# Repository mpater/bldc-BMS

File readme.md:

# VESC BMS
## Overview
Battery Managment System (BMS) for (but not limited to) an Electronic Speed Controller, specifically for a longboard controller (VESC). 

Current battery pack specifications are LiFePO4 (3.2V nominal, ~2.6Ah) in a 6s2p, giving 19.2V with 5Ah (96Wh). Continuous discharge is about 20A (384W) with 30 second pulse discharge of 52A (1kW) and charge current of 5.2A (21.9V), for a 2p configuration.

Scope of the project is to design a BMS to meet the above specifications using off-the-shelf ICs for the battery managment section. A microcontroller circuit would also be incorperated to allow communication between the BMS and controller (SMBus/I2C), contrller and PC (USB-serial) and contrller and VESC (CAN bus).

Texis Instruments (TI) appears to have the most comprehensive set of battery managment systems offerings. These appear to be split up into two main sections: cell monitors and gas gauges. 
The bq769x0 seires will be used for the cell monitoring, offering bq76920, bq76930 and bq76940 based on the pack size. 
Currently the top candidats for the gas gauge are bq78350-R1 and bq34z100-R1 but more research is needed to determine which one is better suited. 

## BMS
- **Cell Monitor**
  - Measure cell voltages and pack current (Coulomb Counter)
  - Cell and temperature measurment
  - Charge Limit (over-voltage and over-amperage)
  - Discharge Limit (under-Voltage and over-amperage)
  - Balancing circuitry and autobalancing mode
  - 
- **'Gas Gauge' and Battery Managment Controller**
  - Estimate pack State of Charge (SoC)
  - Estimate pack State of Health (SoH)
  - Estimate time-to-empty
  - Lifetime datalogging
  - Aging compensation (optional)
  - Self-discharge compensation (optional)

### Cell Monitor
**bq76930**
- 6-19 cells, various chemistries
- 0x08 I2C Address (7-bit), 2.5V LDO, No CRC, 30-TSSOP (PW)
- PN bq7693000DBT

### Gas Gauge

#### bq78350-R1 - Gas Gauge via CEDV
See Technical Reference Sections:
- 9.1.11 - EDV Age Fator - Compensate for cell aging
- 9.1.12 - Self Discharge - estimate self-discharge

#### bq34z100-R1 - Gas Gauge via Impedance Track
'Impedance Track' module from TI give aging compensation and self-discharge compensation -> not true, bq78350 also has this. 
This module does not interface with cell monitor and reads only pack volage, how does it konw self-discharge issues?

## Microcontroller
The MCU provides a communiciton bridge between the gas gauge and PC (serial via USB) and gas gauge and VESC (CAN bus). The MCU does not need to be powered when either of these functions are not used, thus power to operate the MCU should come from either one of these communiciton ports. 
(or have MCU sleep when USB-serial timeout or CAN timeout? Wake-up via interrupt on button or USB-serial or CAN? Seems complicated.)

Firware updates done via SWD or Device firmware update via [USB DFU](http://www.st.com/content/ccc/resource/technical/document/application_note/6a/17/92/02/58/98/45/0c/CD00264379.pdf/files/CD00264379.pdf/jcr:content/translations/en.CD00264379.pdf).

STM32F072C8T6TR
CAN, HDMI-CEC, I²C (SMBus), IrDA, LIN, SPI, UART/USART, USB
IC MCU 32BIT 64KB FLASH 48LQFP
ARM® Cortex®-M0 STM32F0 Microcontroller IC 32-Bit 48MHz 64KB (64K x 8) FLASH 48-LQFP (7x7)

## Reference Projects
- TI Reference Design - TIDA-00449
- TI Reference Design - TIDA-00792
- TI Reference Disign - TIDA-00255
- LibreSolar
  - Also using bq769x0 for cell monitor but no gas gauge, that function is done by the MCU (STM32F072)

## TODO
- [x] Determine pack size and output - see intro
- [x] Determine cell monitor - bq76930
- [x] Determine gas gauge - bq78350-R1 or bq34z100-R1
- [x] Determine MCU - STM32F072 (USB-to-serial, USB bootloader, I2C, CAN)
- [x] 100% - Schematic capture
   - [x] Add pre-charge circuit
   - [x] Change balancing circuit from PNP to NPN
   - [x] Change power-stange layout to POS rail on top of sheet
   - [x] Setup for 6s? or have populated bypass for this layout
   - [x] Press button to show SoC LED display with gas-gauge?
   - [x] Jumper for MCU to be powered by pack
- [x] 100% - BoM and footprint selection for PCB
- [x] 1000% - Determine PCB footprint size constraights (multiple of 26650 cell size)
- [x] 100% - PCB capture
- [ ] 0% - write driver for gas gauge on MCU
- [ ] 0% - write interface module for MCU to PC
- [x] 100% - Order PCB and components
- [x] 100% - Assemble components on PCB
- [x] 100% - Hardware validation testing
- [ ] TI SMBus to PC moudule is very expensive, looking for something similar to view BMS status

## PCB_2019-06 TOFIX
- [ ] Swap I2C's on STM32F0 as I2C1 only support SMBus for bq78350-r1
- [ ] Mirror STM32F0 debug conn pinout
- [ ] Assemble and test PCB

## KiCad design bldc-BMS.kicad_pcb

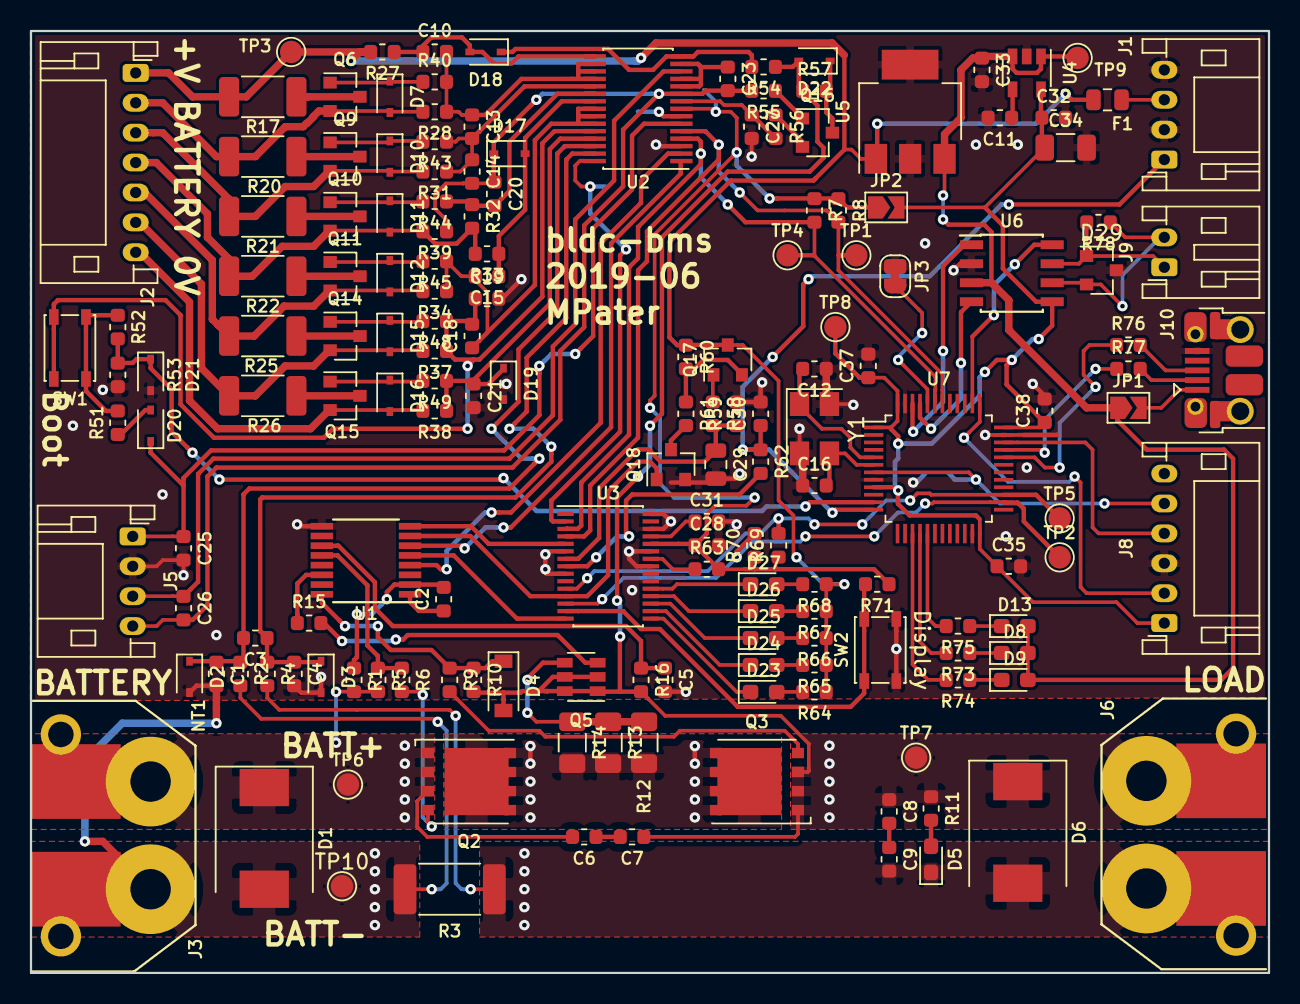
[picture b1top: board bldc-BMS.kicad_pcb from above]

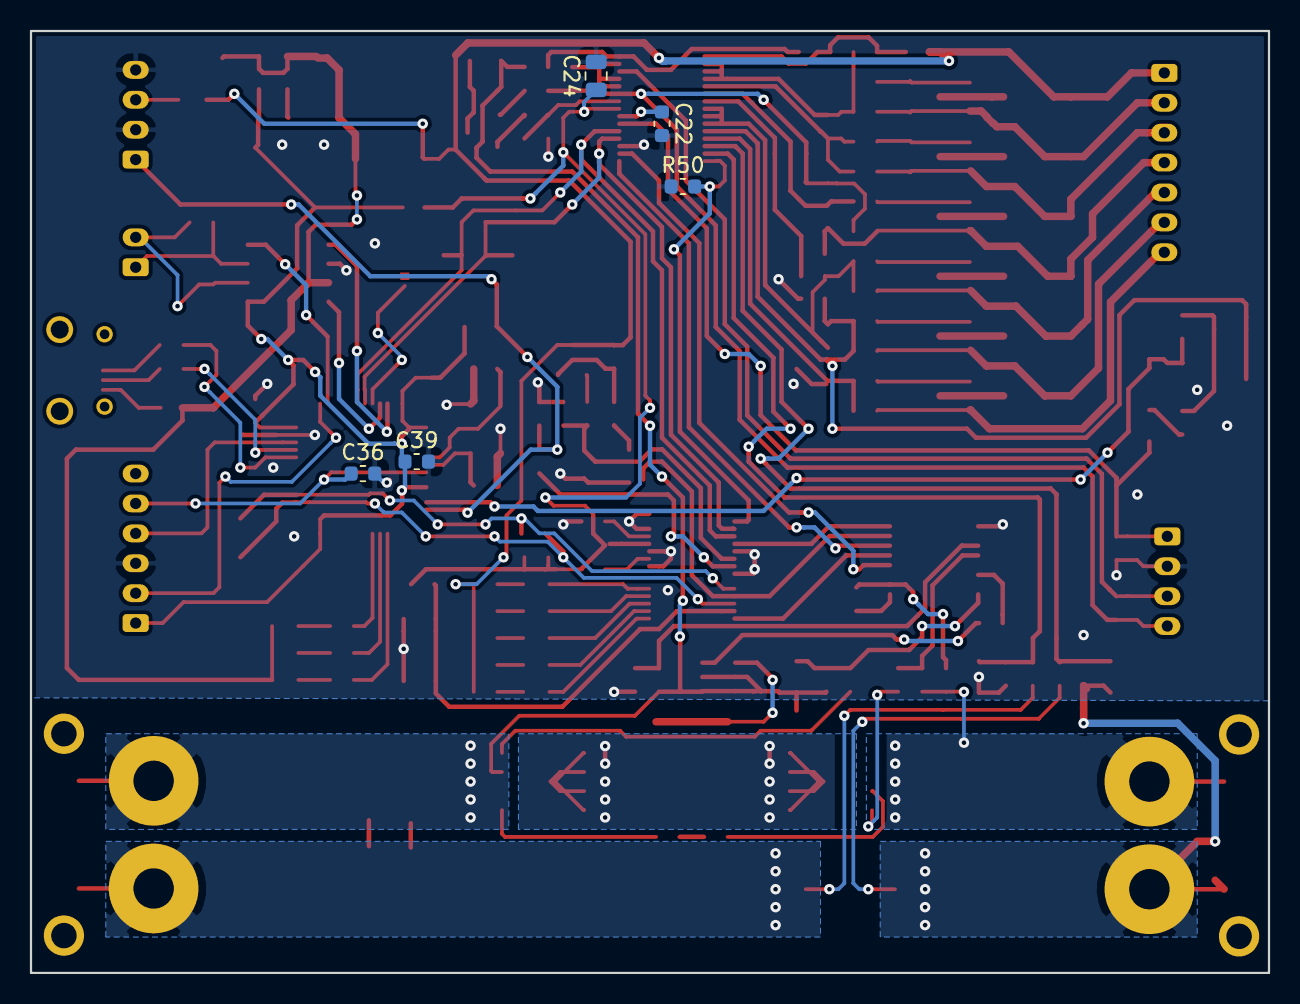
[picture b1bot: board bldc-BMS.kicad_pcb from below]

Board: 2 copper layers, 82.8 x 63.0 mm, 175 parts (5 on the bottom side), 117 nets.

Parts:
C1, C3, C4, C6, C7, C8, C9, C28, C30, C31, C35, C36, C37, C38, C39: 0.1uF; C_0603_1608Metric
C2, C10, C13, C14, C15, C18, C19, C20, C21, C22, C23, C27: 1uF 10V; C_0603_1608Metric
C5: 0.01uF; C_0603_1608Metric
C11: 470nF; C_0603_1608Metric
C12, C16: 15pF; C_0603_1608Metric
C24: 4.7uF; C_0805_2012Metric
C25, C26: 4.7nF; C_0603_1608Metric
C29: 3.3uF; C_0805_2012Metric
C32, C33: 2.2uF; C_0603_1608Metric
C34: 100uF; C_1206_3216Metric
D1: SMCJ45A; D_SMC
D2, D3, D19: 3.3V; D_SOD-323
D4: MMSZ5246B-7-F; D_SOD-123
D5, D9, D23, D24, D25, D26, D27: GREEN; LED_0603_1608Metric_Pad1.05x0.95mm_HandSolder
D6: MURS360T3G; D_SMC
D7, D10, D11, D12, D15, D16, D21: 5.6V; D_SOD-323
D8: RED; LED_0603_1608Metric_Pad1.05x0.95mm_HandSolder
D13: BLUE; LED_0603_1608Metric_Pad1.05x0.95mm_HandSolder
D17, D18, D20, D22: 1N4148W; D_SOD-323
D29: D_TVS_x2_AAC; D_SOT-23_TVS
F1: 100mA; Fuse_0805_2012Metric
J1, J5: Conn_01x04; JST_PH_S4B-PH-K_1x04_P2.00mm_Horizontal
J2: Conn_01x07; JST_PH_S7B-PH-K_1x07_P2.00mm_Horizontal
J3: XT60_MALE; XT60PW-M20
J6: XT60_FEMALE; XT60PW-F20
J8: Conn_01x06; JST_PH_S6B-PH-K_1x06_P2.00mm_Horizontal
J9: Conn_01x02; JST_PH_S2B-PH-K_1x02_P2.00mm_Horizontal
J10: USB_B_Micro; USB_Micro-B_Amphenol_10103594-0001LF_Horizontal_circular
JP1, JP2: Jumper_NO; SolderJumper-2_P1.3mm_Open_TrianglePad1.0x1.5mm
JP3: Jumper_NC_Small; SolderJumper-2_P1.3mm_Bridged_RoundedPad1.0x1.5mm
NT1: Net-Tie; NetTie-2_SMD_Pad0.5mm
Q2, Q3: CSD18531Q5A; TDSON-8-1
Q5: Q_PMOS; SOT-23-6
Q6, Q9, Q10, Q11, Q14, Q15, Q16, Q18: Q_NMOS_GSD; SOT-23
Q17: ZXMP10A13FTA; SOT-23
R1, R2, R4, R16, R54, R56: 100R; R_0603_1608Metric
R3: 0.005R; R_2512_6332Metric_Pad1.52x3.35mm_HandSolder
R5, R10: 1M; R_0603_1608Metric
R6, R9, R15, R73, R74: 220R; R_0603_1608Metric
R7, R8, R50, R53, R55, R57, R60, R63, R69, R70, R71: 100k; R_0603_1608Metric
R11, R64, R65, R66, R67, R68: 2k; R_0603_1608Metric
R12, R13, R14: 1k; R_1206_3216Metric
R17, R20, R21, R22, R25, R26: 33R; R_2010_5025Metric
R27, R28, R31, R32, R33, R34, R37, R38, R39: 1k 1%; R_0603_1608Metric
R40, R43, R44, R45, R48, R49, R51, R52: 10k; R_0603_1608Metric
R58, R59: 300k; R_0603_1608Metric
R61: 220k; R_0603_1608Metric
R62, R75: 1k; R_0603_1608Metric
R76, R77: 22R; R_0603_1608Metric
R78: 120R; R_0603_1608Metric
SW1, SW2: SW_Push; SW_SPST_PTS810
TP1: SCL; TestPoint_Pad_D1.5mm
TP2: SMBC; TestPoint_Pad_D1.5mm
TP3: REGOUT; TestPoint_Pad_D1.5mm
TP4: SDA; TestPoint_Pad_D1.5mm
TP5: SMBD; TestPoint_Pad_D1.5mm
TP6: BAT+; TestPoint_Pad_D1.5mm
TP7: LOAD+; TestPoint_Pad_D1.5mm
TP8: 3.3V; TestPoint_Pad_D1.5mm
TP9: 5V; TestPoint_Pad_D1.5mm
TP10: BAT-; TestPoint_Pad_D1.5mm
U1: bq76200; TSSOP-16_4.4x5mm_P0.65mm
U2: bq76930; TSSOP-30_4.4x7.8mm_P0.5mm
U3: BQ78350-R1; TSSOP-30_4.4x7.8mm_P0.5mm
U4: MIC5219-3.3; SOT-23-5
U5: MIC5239-5.0; SOT-223
U6: TJA1042T-3; SOIC-8_3.9x4.9mm_P1.27mm
U7: STM32F072C8; LQFP-48_7x7mm_P0.5mm
Y1: 8MHz; Crystal_SMD_5032-4Pin_5.0x3.2mm

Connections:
+3V3: C32.1, C34.1, C35.1, C37.1, C38.1, C39.1, J8.1, JP2.2, TP8.1, U4.5, U6.5, U7.1, U7.9, U7.24, U7.36, U7.48
+5V: C33.1, D8.2, D9.2, D13.2, JP1.1, TP9.1, U4.1, U4.3, U5.3, U6.3
/Battery Controller/ALERT: R50.2, U2.30, U3.2
/Battery Controller/C10: F1.1, J2.1, Q17.3, R17.2, R27.2, R60.1, R64.1, R65.1, R66.1, R67.1, R68.1, TP3.1, U5.1
/Battery Controller/CP_EN: U1.5, U3.15
/Battery Controller/PCHG: U1.8, U3.5
/Battery Controller/PMON_EN: Q18.1, U1.7, U3.12
/Battery Controller/REGOUT: C24.1, C28.1, JP2.1, R7.1, R8.1, R63.2, R69.1, R70.1, R71.1, U2.8, U3.26
/Battery Controller/~ENABLE: C30.1, J1.1, R62.1, U7.12
/Battery Monitor/BAT: D18.1, R54.2, U2.15
/Battery Monitor/BOOT_RETURN: R51.1, R52.2, SW1.2
/Battery Monitor/BOOT_SUPPLY: C18.2, C19.1, R37.1, R48.1, SW1.1, U2.26
/Battery Monitor/C0: D16.2, J2.7, Q15.2, R38.2
/Battery Monitor/C1: D15.2, J2.6, Q14.2, R26.2, R37.2
/Battery Monitor/C2: D12.2, J2.5, Q11.2, R25.2, R34.2
/Battery Monitor/C5: D11.2, J2.4, Q10.2, R22.2, R32.2, R33.2, R39.2
/Battery Monitor/C6: D10.2, J2.3, Q9.2, R21.2, R31.2
/Battery Monitor/C7: D7.2, J2.2, Q6.2, R20.2, R28.2
/Battery Monitor/CHG: U1.4, U2.2
/Battery Monitor/DSG: U1.6, U2.1
/Battery Monitor/LOAD+: C7.1, C8.1, D4.2, D6.1, D22.2, J6.1, Q3.1, Q3.2, Q3.3, Q5.1, Q5.2, Q5.5, Q5.6, R10.2, R11.1, R16.2, R54.1, R57.1, TP7.1
/Battery Monitor/NTC2: C26.1, J5.3, U2.13
/Battery Monitor/NTC_1: C25.1, D20.1, J5.1, U2.6
/Battery Monitor/NTC_2_GND: C14.2, C20.1, C23.2, C26.2, D17.1, J5.4, R39.1, R55.2, U2.10
/Battery Monitor/REGSRC: C27.1, R56.2, U2.9
/Battery Monitor/SRN: C3.1, C4.1, D3.1, R4.1, U2.29
/Battery Monitor/SRP: C1.1, C3.2, D2.1, R2.1, U2.28
/Battery Monitor/VC0: C21.1, D19.1, R38.1, R49.1, U2.27
/Battery Monitor/VC4: C15.2, C18.1, R34.1, R45.1, U2.23, U2.24, U2.25
/Battery Monitor/VC5: C15.1, D17.2, R33.1, U2.22
/Battery Monitor/VC5B: C20.2, R32.1, R44.1, U2.21
/Battery Monitor/VC6: C13.2, C14.1, R31.1, R43.1, U2.20
/Battery Monitor/VC9: C10.2, C13.1, R28.1, R40.2, U2.17, U2.18, U2.19
/Battery Monitor/VC10: C10.1, D18.2, R27.1, U2.16
/Battery Monitor/WAKE: D21.1, R52.1, R53.2, U7.11
/CAN and USB Interface/CAN_H: D29.1, J9.1, R78.2, U6.7
/CAN and USB Interface/CAN_L: D29.2, J9.2, R78.1, U6.6
/CAN and USB Interface/CAN_RX: U6.4, U7.45
/CAN and USB Interface/CAN_STB: U6.8, U7.38
/CAN and USB Interface/CAN_TX: U6.1, U7.46
/CAN and USB Interface/I2C1_SCL: R8.2, TP1.1, U2.5, U3.4, U7.42
/CAN and USB Interface/I2C1_SDA: R7.2, TP4.1, U2.4, U3.3, U7.43
/CAN and USB Interface/I2C2_SCL: R70.2, TP2.1, U3.13, U7.26
/CAN and USB Interface/I2C2_SDA: R69.2, TP5.1, U3.11, U7.27
/CAN and USB Interface/LED_BLUE: R75.2, U7.17
/CAN and USB Interface/LED_GREEN: R74.2, U7.15
/CAN and USB Interface/LED_RED: R73.2, U7.16
/CAN and USB Interface/SWCLK: J8.2, U7.37
/CAN and USB Interface/SWDIO: J8.4, U7.34
/CAN and USB Interface/USB_DM: J10.2, R77.2
/CAN and USB Interface/USB_DP: J10.3, R76.2
/CAN and USB Interface/~RST: C36.1, J8.5, U7.7
/Power Stage/BAT+: C6.2, D1.1, J3.1, Q2.1, Q2.2, Q2.3, R1.2, R5.2, TP6.1
/Power Stage/BAT-: D1.2, J3.2, NT1.1, R2.2, R3.1, TP10.1
/Power Stage/LOAD-: C9.2, D5.1, D6.2, J6.2, R3.2, R4.2
GND: C1.2, C4.2, C5.2, C11.2, C12.1, C16.1, C19.2, C21.2, C22.2, C24.2, C25.2, C27.2, C28.2, C29.2, C30.2, C31.2, C32.2, C33.2, C34.2, C35.2, C36.2, C37.2, C38.2, C39.2, D2.2, D3.2, D19.2, D21.2, D29.3, J1.2, J1.4, J5.2, J8.3, J10.5, JP3.1, NT1.2, Q18.2, R50.1, R53.1, R59.2, SW2.2, U1.9, U2.3, U3.6, U3.9, U3.21, U3.22, U3.23, U3.25, U3.28, U3.30, U4.2, U5.2, U6.2, U7.8, U7.23, U7.35, U7.47, Y1.2, Y1.4
unnamed: C2.1, U1.1
unnamed: C2.2, R1.1, U1.2
unnamed: C5.1, R16.1, U1.11
unnamed: C6.1, C7.2
unnamed: C8.2, C9.1
unnamed: C11.1, U4.4
unnamed: C12.2, U7.5, Y1.1
unnamed: C16.2, U7.6, Y1.3
unnamed: C22.1, U2.7
unnamed: C23.1, U2.11, U2.12, U2.14
unnamed: C29.1, R58.2, R59.1, U3.7
unnamed: C31.1, U3.27
unnamed: D4.1, R9.1, R10.1, U1.16
unnamed: D5.2, R11.2
unnamed: D7.1, Q6.1, R40.1
unnamed: D8.1, R73.1
unnamed: D9.1, R74.1
unnamed: D10.1, Q9.1, R43.2
unnamed: D11.1, Q10.1, R44.2
unnamed: D12.1, Q11.1, R45.2
unnamed: D13.1, R75.1
unnamed: D15.1, Q14.1, R48.2
unnamed: D16.1, Q15.1, R49.2
unnamed: D20.2, R51.2
unnamed: D22.1, Q16.3, R57.2
unnamed: D23.1, U3.16
unnamed: D23.2, R64.2
unnamed: D24.1, U3.17
unnamed: D24.2, R65.2
unnamed: D25.1, U3.18
unnamed: D25.2, R66.2
unnamed: D26.1, U3.19
unnamed: D26.2, R67.2
unnamed: D27.1, U3.20
unnamed: D27.2, R68.2
unnamed: F1.2, J1.3
unnamed: J10.1, JP1.2
unnamed: JP3.2, U7.44
unnamed: Q2.4, R6.2
unnamed: Q2.5, Q3.5, R12.2, R13.2, R14.2
unnamed: Q3.4, R9.2
unnamed: Q5.3, R15.2
unnamed: Q5.4, R12.1, R13.1, R14.1
unnamed: Q6.3, R17.1
unnamed: Q9.3, R20.1
unnamed: Q10.3, R21.1
unnamed: Q11.3, R22.1
unnamed: Q14.3, R25.1
unnamed: Q15.3, R26.1
unnamed: Q16.1, R55.1
unnamed: Q16.2, R56.1
unnamed: Q17.1, R58.1
unnamed: Q17.2, R60.2, R61.1
unnamed: Q18.3, R61.2
unnamed: R5.1, R6.1, U1.12
unnamed: R15.1, U1.14
unnamed: R62.2, U3.8
unnamed: R63.1, U3.24
unnamed: R71.2, SW2.1, U3.14
unnamed: R76.1, U7.32
unnamed: R77.1, U7.33

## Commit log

2018-06-24 readme formatting corrections and adding schematic PDF
2018-06-25 Update readme.md
    Corrected typo
2018-09-02 Updated top-level connections and added MCU
2019-06-28 Good-enough for first PCB attempt.
2019-08-23 first PCB spin for testing
2019-08-23 added test PCB note
2019-08-23 added schematic pdf
